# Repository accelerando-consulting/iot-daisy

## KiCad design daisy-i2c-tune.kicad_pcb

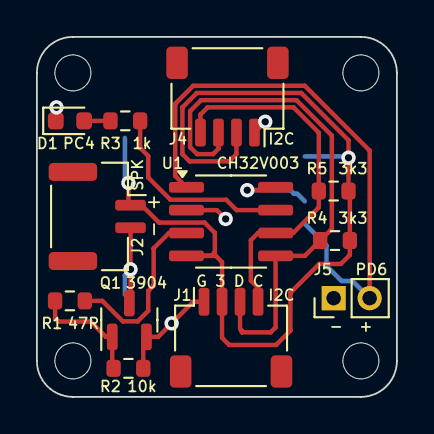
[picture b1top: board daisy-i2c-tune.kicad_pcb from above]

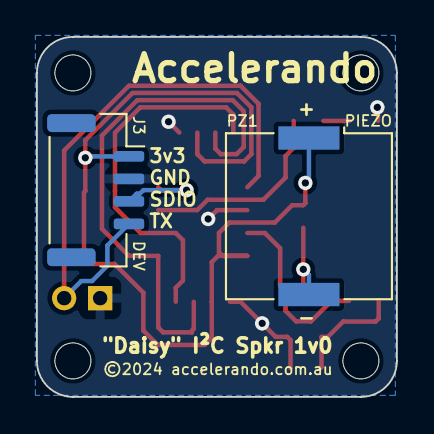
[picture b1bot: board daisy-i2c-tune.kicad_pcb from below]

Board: 2 copper layers, 20.0 x 20.0 mm, 18 parts (2 on the bottom side), 11 nets.

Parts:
D1: PC4; LED_0603_1608Metric
H1, H2, H3, H4: MountingHole; MountingHole_2.0mm
J1, J4: I2C; JST_SH_SM04B-SRSS-TB_1x04-1MP_P1.00mm_Horizontal
J2: SPK; JST_GH_SM02B-GHS-TB_1x02-1MP_P1.25mm_Horizontal
J3: DEV; JST_GH_SM04B-GHS-TB_1x04-1MP_P1.25mm_Horizontal
J5: PD6; PinHeader_1x02_P2.00mm_Vertical
PZ1: PIEZO; Buzzer_Murata_PKMCS0909E
Q1: 3904; SOT-23
R1: 47R; R_0603_1608Metric
R2: 10k; R_0603_1608Metric
R3: 1k; R_0603_1608Metric
R4, R5: 3k3; R_0603_1608Metric
U1: CH32V003; SOIC-8_3.9x4.9mm_P1.27mm

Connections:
+3V3: J1.2, J2.1, J3.1, J4.2, PZ1.1, R4.2, R5.2, U1.4 (VDD)
/AUDIO: R1.2, U1.3 (PA2)
/BASE: Q1.1 (B), R1.1, R2.2
/LED: R3.1, U1.7 (PC4)
/LEDA: D1.2 (A), R3.2
/SCL: J1.4, J4.4, R5.1, U1.6 (PC2)
/SDA: J1.3, J4.3, R4.1, U1.5 (PC1)
/SDIO: J3.3, U1.8 (PD4)
/SPKR-: J2.2, PZ1.2, Q1.3 (C)
/TX: J3.4, J5.2, U1.1 (PD6)
GND: D1.1 (K), J1.1, J3.2, J4.1, J5.1, Q1.2 (E), R2.1, U1.2 (VSS)

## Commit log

2024-06-28 Daisy I2C chiptune module
2024-07-12 i2c_eeprom.c - Working code for i2c write/read with AT24C32
2024-07-12 i2c_eeprom.c - Fine tuning of eeprom test for fastest result
2024-07-12 i2c_eeprom.c - Go faster
2024-07-16 I2C read and write now working
2024-07-23 Working slave speaker code
2024-07-23 Support for sdi/uart/none debug output

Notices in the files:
daisy-i2c-tune.kicad_pcb:
©2024 accelerando.com.au
